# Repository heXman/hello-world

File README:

first git test
nog een regel in readme

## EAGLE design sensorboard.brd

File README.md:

hello-world
===========

This is our new brqnch proposal

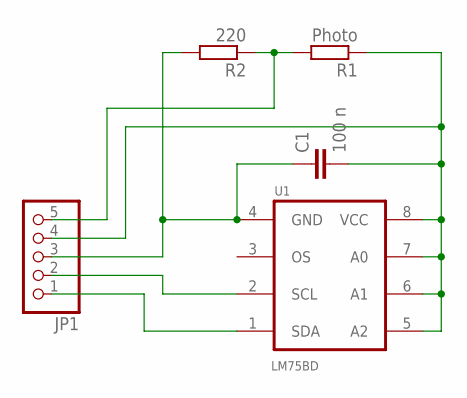
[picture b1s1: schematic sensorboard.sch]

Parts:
C1: 100 n; C0805
JP1: PINHD-1X5/90; 1X05/90
R1: Photo; 0207/15
R2: 220; R0805
U1: LM75BD; SOIC127P600X175-8N

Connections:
unnamed: C1.1, JP1.3, R2.2, U1.4 (GND)
unnamed: C1.2, JP1.4, R1.1, U1.5 (A2), U1.6 (A1), U1.7 (A0), U1.8 (VCC)
unnamed: JP1.2, U1.2 (SCL)
unnamed: JP1.1, U1.1 (SDA)
unnamed: JP1.5, R1.2, R2.1

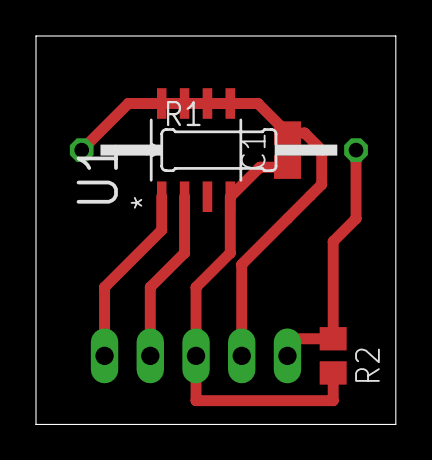
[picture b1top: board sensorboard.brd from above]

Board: 2 copper layers, 20.0 x 21.6 mm, 5 parts (1 on the bottom side), 5 nets.

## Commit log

2013-03-13 first thing committed
2013-04-16 edit files
2017-04-06 Update README.md
    modified the readme
2017-04-06 Add files via upload
    Sensortboard project files
